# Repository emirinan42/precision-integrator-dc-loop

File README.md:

# Precision Integrator with DC Feedback Loop

High-precision active integrator design incorporating a DC feedback loop to attenuate offset drift, suppress low-frequency instability, and maintain closed-loop AC stability.

## Key Specifications & Hardware
- **Operational Amplifier:** LTC6268 (Low-noise, high-speed op-amp)
- **Topology:** Active integrator with reset switch network and DC feedback loop
- **EDA & Simulation Tools:** LTspice, Cadence Virtuoso, KiCad

## Simulation Results & Plots

### AC Analysis (Bode Plot)
Shows closed-loop bandwidth, low-frequency offset suppression, and phase margin stability.

---

### Transient Response
Time-domain output behavior under reset switch pulses.

## How to Run Simulations
1. Download the `.asc` simulation file from this repository.
2. Open with **LTspice**.
3. Run `.ac` analysis for stability checking or `.tran` for time-domain transient behavior.

## PCB Layout & Hardware Implementation

A custom 2-layer low-noise PCB layout was designed to validate LTspice simulations with real-world hardware.

### 3D Board View

### Layout Considerations & Noise Mitigation
- **High-Impedance Node Shielding:** Sensitive feedback trace connected to the LTC6268 inverting input was isolated with a ground guard ring to minimize parasitic capacitance and leakage currents.
- **Power Integrity:** Placed low-ESR bypass capacitors (100nF and 10µF) in close proximity to the op-amp power supply pins to suppress high-frequency power-rail noise.
- **Grounding Strategy:** Dedicated solid ground plane on the bottom layer to reduce ground loop inductance.

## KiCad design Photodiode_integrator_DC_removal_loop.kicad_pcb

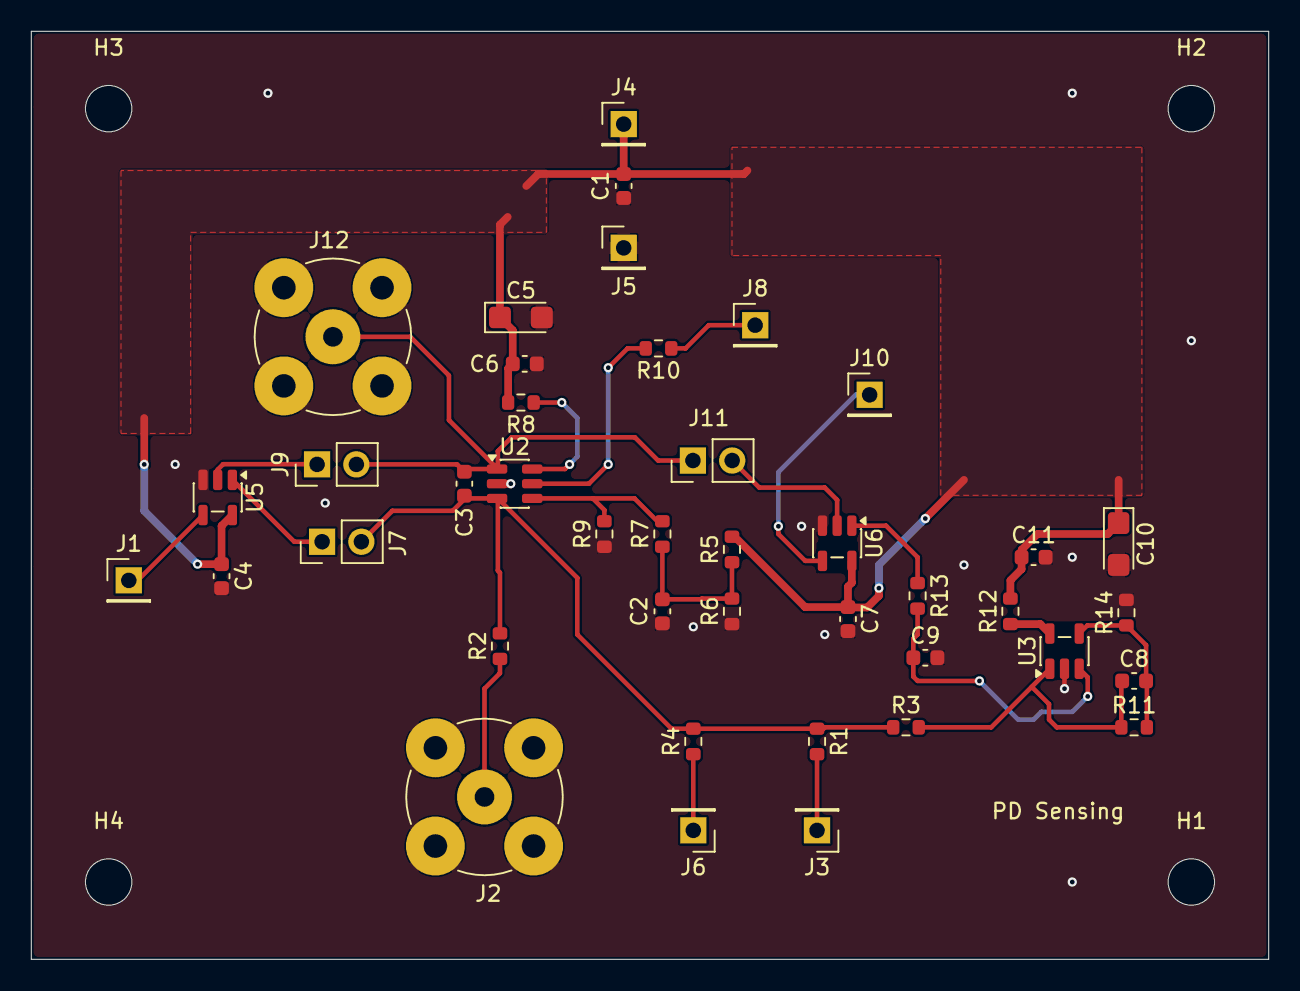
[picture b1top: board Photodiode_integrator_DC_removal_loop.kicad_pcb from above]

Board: 2 copper layers, 80.0 x 60.0 mm, 45 parts (0 on the bottom side), 22 nets.

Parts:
C1: 10u; C_0603_1608Metric
C2: 470u; C_0603_1608Metric
C3: 1p; C_0603_1608Metric
C4, C6, C7, C11: 0.1u; C_0603_1608Metric
C5, C10: 4.7u; CP_EIA-3216-18_Kemet-A
C8: 100n; C_0603_1608Metric
C9: 100u; C_0603_1608Metric
H1, H2, H3, H4: MountingHole; MountingHole_3mm
J1, J3, J4, J5, J6, J8, J10: Conn_01x01_Pin; PinHeader_1x01_P2.54mm_Vertical
J2, J12: Conn_Coaxial_Power; BNC_TEConnectivity_1478204_Vertical
J7, J9, J11: Conn_01x02_Pin; PinHeader_1x02_P2.54mm_Vertical
R1, R2, R4, R8, R12: 10; R_0603_1608Metric
R3: 1k; R_0603_1608Metric
R5, R6: 100k; R_0603_1608Metric
R7, R9, R10: 0; R_0603_1608Metric
R11, R13: 10k; R_0603_1608Metric
R14: 20k; R_0603_1608Metric
U2: LTC6268; TSOT-23-6
U3: AD8065; SOT-23-5
U5, U6: MAX4504CUK+; SOT-23-5

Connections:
+5V: C1.1, C4.1, C5.1, C6.1, C7.1, C10.1, C11.1, J4.1 (Pin_1_1), R5.2, R8.2, R12.2, U5.5 (V+), U6.5 (V+)
/SHDN: R10.2, U2.5 (SHDN)
/Vnode: C8.1, R3.2, R11.1, U3.1
/Vout: C3.1, J9.2, J11.1, J12.1 (In), U2.1 (OUT)
/Vsw: J1.1 (Pin_1_1), U5.4 (IN)
GND: C1.2, C2.2, C4.2, C5.2, C6.2, C7.2, C9.2, C10.2, C11.2, J2.2 (Ext), J5.1 (Pin_1_1), J12.2 (Ext), R6.1, R9.1, R14.2, U2.2 (V-), U3.2 (V-), U5.3 (V-), U6.3 (V-)
unnamed: C2.1, R5.1, R6.2, R7.1
unnamed: J2.1 (In), R2.1
unnamed: J3.1 (Pin_1_1), R1.2
unnamed: J6.1 (Pin_1_1), R4.1
unnamed: J7.1, U5.1 (COM)
unnamed: C3.2, J7.2, R1.1, R2.2, R3.1, R4.2, U2.3 (+IN)
unnamed: J8.1 (Pin_1_1), R10.1
unnamed: J9.1, U5.2 (NC)
unnamed: J10.1 (Pin_1_1), U6.4 (IN)
unnamed: J11.2, U6.2 (NC)
unnamed: R7.2, R9.2, U2.4 (-IN)
unnamed: R8.1, U2.6 (V+)
unnamed: C9.1, R13.2, U3.3 (+)
unnamed: C8.2, R11.2, R14.1, U3.4 (-)
unnamed: R12.1, U3.5 (V+)
unnamed: R13.1, U6.1 (COM)
